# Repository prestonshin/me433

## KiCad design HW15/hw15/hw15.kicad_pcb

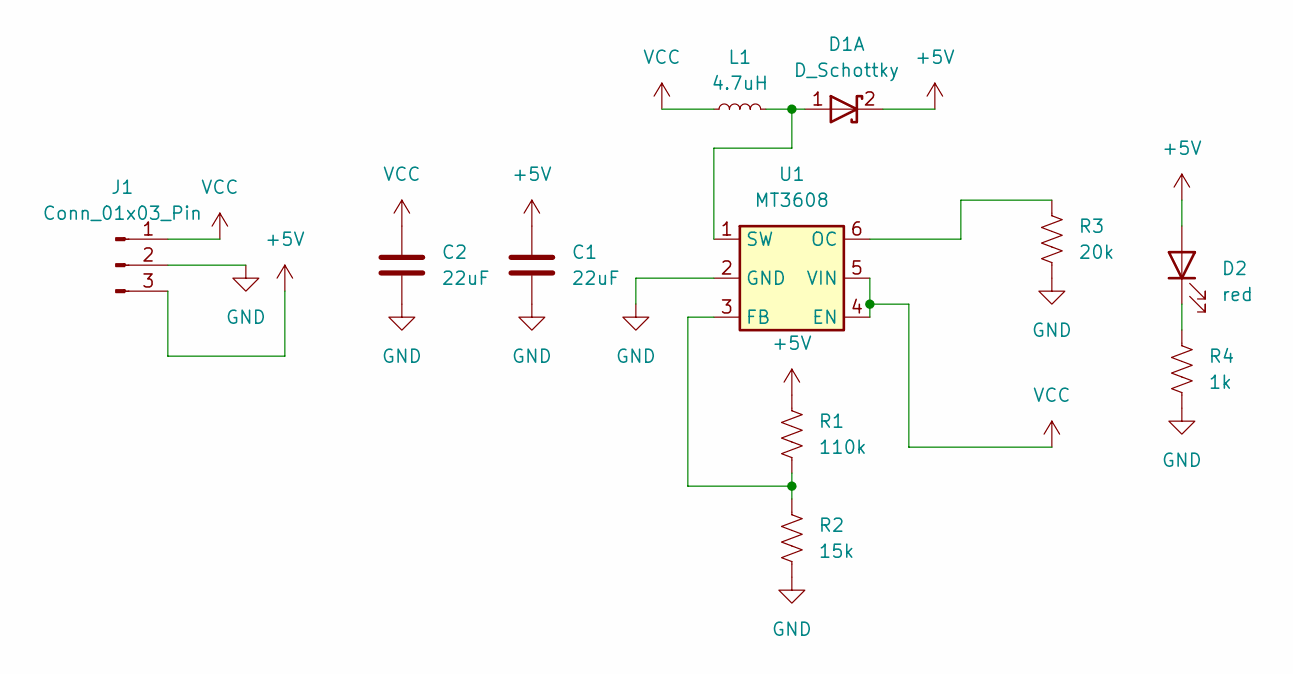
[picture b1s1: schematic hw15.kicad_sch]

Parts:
C1, C2: 22uF; CP_Elec_8x6.2
D1: D_Schottky; D_3220_8050Metric_Pad2.65x5.15mm_HandSolder
D2: red; LED_D2.0mm_W4.8mm_H2.5mm_FlatTop
J1: Conn_01x03_Pin; PinSocket_1x03_P2.54mm_Vertical
L1: 4.7uH; L_1206_3216Metric
R1: 110k; R_0805_2012Metric_Pad1.20x1.40mm_HandSolder
R2: 15k; R_0805_2012Metric_Pad1.20x1.40mm_HandSolder
R3: 20k; R_0805_2012Metric_Pad1.20x1.40mm_HandSolder
R4: 1k; R_0805_2012Metric_Pad1.20x1.40mm_HandSolder
U1: MT3608; SOT-23-6

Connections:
+5V: C1.1, D1.2 (K), D2.2 (A), J1.3, R1.1
GND: C1.2, C2.2, J1.2, R2.2, R3.2, R4.2, U1.2 (GND)
unnamed: D1.1 (A), L1.2, U1.1 (SW)
unnamed: D2.1 (K), R4.1
unnamed: R1.2, R2.1, U1.3 (FB)
unnamed: R3.1, U1.6 (OC)
VCC: C2.1, J1.1, L1.1, U1.4 (EN), U1.5 (VIN)

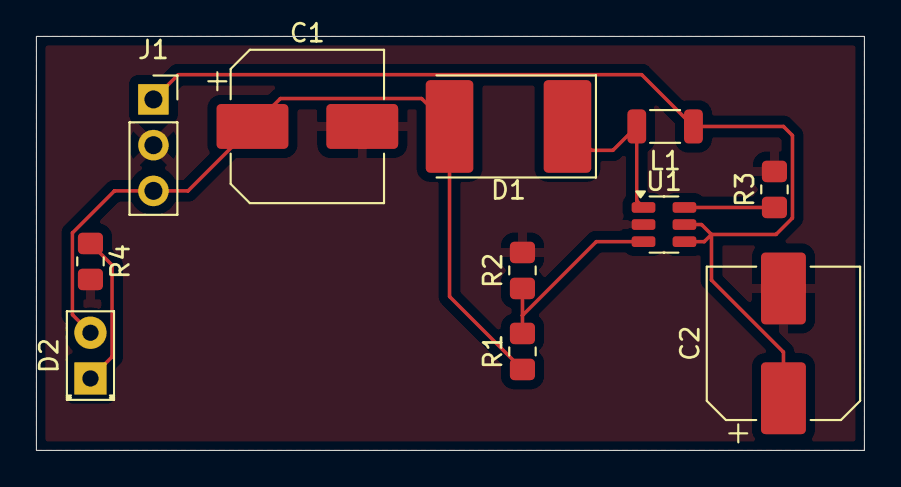
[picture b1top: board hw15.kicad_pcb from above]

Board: 2 copper layers, 46.0 x 23.0 mm, 11 parts (0 on the bottom side), 7 nets.

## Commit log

2025-04-08 hw2 not working - button
2025-04-08 did hw2
2025-04-11 did somethiong idk
2025-04-14 hw3 might work?
2025-04-15 hw3 done
2025-04-16 started 4
2025-05-14 started code and finished 6
2025-05-16 done with hw7
2025-05-26 done w 10
2025-05-28 hw9 done
2025-05-31 4 done
2025-06-03 done with 13 and 5
2025-06-03 done w cad
2025-06-04 done with pcb
2025-06-05 did camera stuff
